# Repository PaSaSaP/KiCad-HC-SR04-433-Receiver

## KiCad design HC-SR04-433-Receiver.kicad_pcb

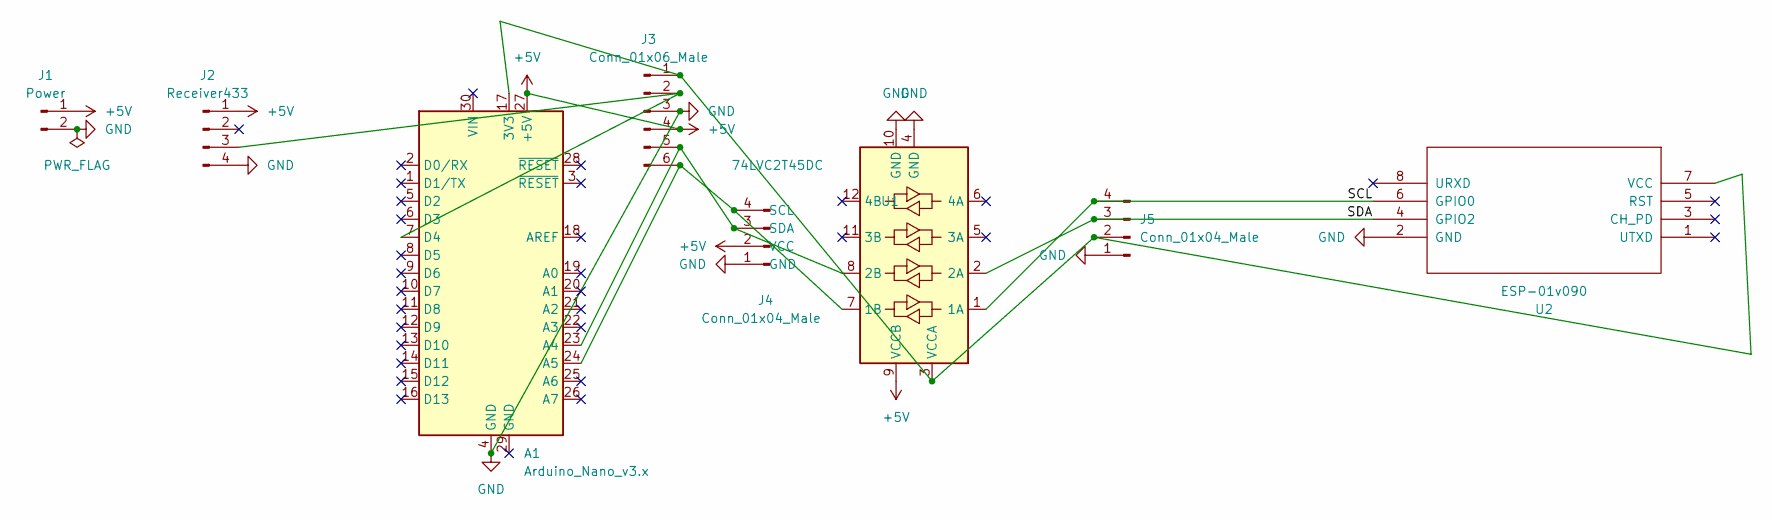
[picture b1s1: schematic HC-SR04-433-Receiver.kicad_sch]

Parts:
A1: Arduino_Nano_v3.x; Arduino_Nano
J1: Power
J2: Receiver433
J3: Conn_01x06_Male
J4, J5: Conn_01x04_Male; PinHeader_2x04_P2.54mm_Vertical
U1: 74LVC2T45DC; LevelShifter x04
U2: ESP-01v090; PinSocket_2x04_P2.54mm_Vertical

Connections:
+5V: A1.27 (+5V), J1.1, J2.1, J3.4, J4.2 (VCC), U1.9 (VCCB)
/SCL: J5.4, U1.1 (1A), U2.6 (GPIO0)
/SDA: J5.3, U1.2 (2A), U2.4 (GPIO2)
GND: A1.4 (GND), J1.2, J2.4, J3.3, J4.1 (GND), J5.1, U1.4 (GND), U1.10 (GND), U2.2 (GND)
unnamed: A1.7 (D4), J2.3, J3.2
unnamed: A1.17 (3V3), J3.1, J5.2, U1.3 (VCCA), U2.7 (VCC)
unnamed: A1.23 (A4), J3.5, J4.3 (SDA), U1.8 (2B)
unnamed: A1.24 (A5), J3.6, J4.4 (SCL), U1.7 (1B)

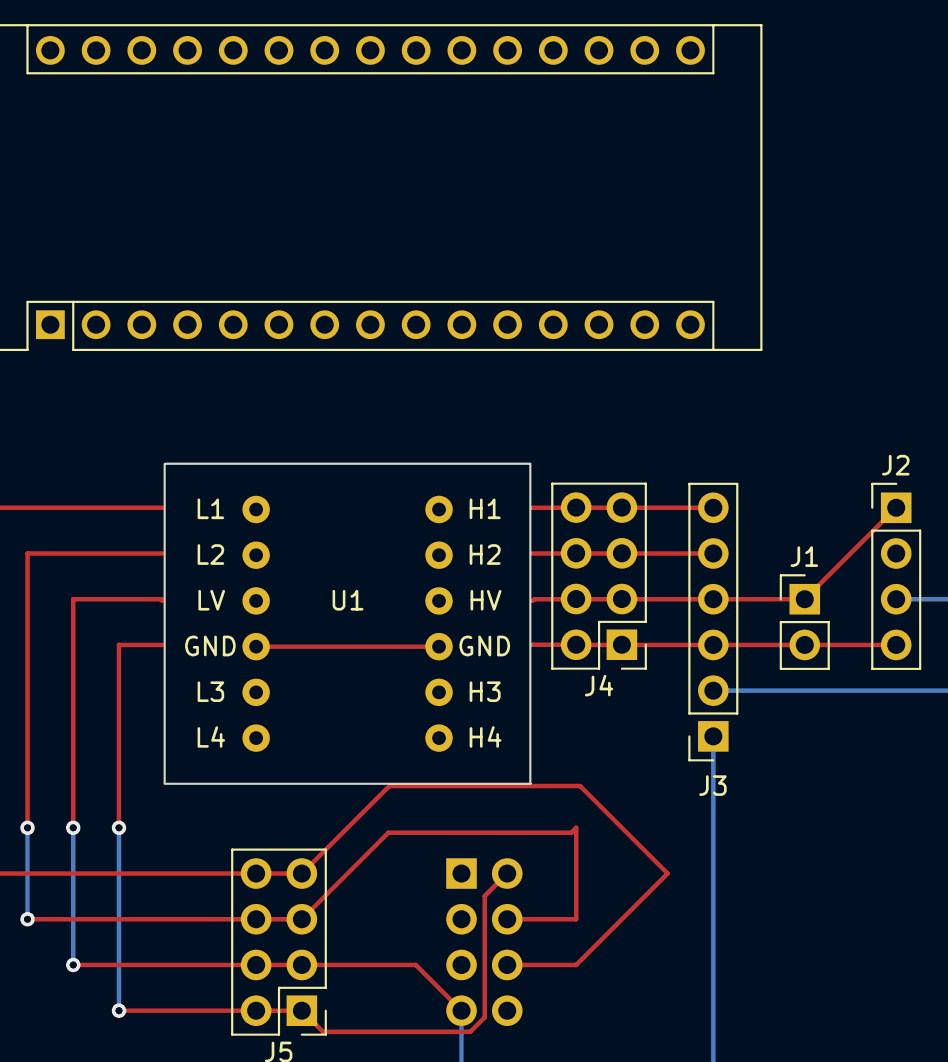
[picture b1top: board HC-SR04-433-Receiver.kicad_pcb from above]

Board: 2 copper layers, 8 parts (1 on the bottom side), 8 nets.
